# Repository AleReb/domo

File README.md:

# Domo — registrador ambiental para ESP32

Domo mide temperatura, humedad y presión, muestra lecturas en una pantalla OLED y guarda archivos CSV diarios en una tarjeta MicroSD. Este documento describe el comportamiento de [domo.ino](domo.ino).

## Componentes

| Componente | Función y configuración del firmware |
| --- | --- |
| SHT40 | Temperatura y humedad por I2C, dirección `0x44`. |
| HMP60 + ADS1115 | Temperatura en A0 y humedad en A1 del ADS1115 (`0x48`), con salidas analógicas de 0–1 V. Ganancia `GAIN_ONE` (rango ±4,096 V). |
| BME280 | Temperatura, humedad y presión por I2C, dirección `0x76`. |
| DHT22 | Temperatura y humedad por GPIO 19. |
| DS3231 | Fecha y hora para la pantalla y el registro. |
| OLED SH1106 de 128 × 64 | Dirección `0x3C`; controlador activo `U8G2_SH1106_128X64_NONAME_F_HW_I2C`. Hay una alternativa SSD1306 comentada en el código. |
| MicroSD | Almacenamiento por SPI, bus HSPI. |

Para el HMP60, el código convierte `temperatura (°C) = mV × 0,1 − 40` y `humedad (% HR) = mV × 0,1`, con humedad limitada a 0–100 %. Comprueba que estas fórmulas correspondan a la configuración de salida del sensor utilizado.

## Conexiones

`Wire.begin()` usa los pines I2C predeterminados de la placa seleccionada. Para el ESP32 Dev Module configurado en el repositorio:

| Interfaz | Señal | Pin ESP32 |
| --- | --- | --- |
| I2C compartido | SDA | GPIO 21 |
| I2C compartido | SCL | GPIO 22 |
| MicroSD / HSPI | MISO | GPIO 2 |
| MicroSD / HSPI | MOSI | GPIO 15 |
| MicroSD / HSPI | CLK | GPIO 14 |
| MicroSD / HSPI | CS | GPIO 13 |
| DHT22 | DATA | GPIO 19 |

Conecta la salida de temperatura del HMP60 a A0 del ADS1115 y la de humedad a A1, con tierra común. Comprueba alimentación, niveles eléctricos y conexiones antes de energizar el montaje. Esta tabla describe el firmware; revisa también el esquema electrónico.

## Compilación y puesta en marcha

1. Abre `domo.ino` desde una carpeta llamada `domo` en Arduino IDE.
2. Instala el paquete de placas **esp32 de Espressif Systems** y selecciona **ESP32 Dev Module** (`esp32:esp32:esp32`). Los artefactos incluidos hacen referencia al core **2.0.17**; las versiones de las bibliotecas no están fijadas en un manifiesto.
3. Instala las bibliotecas indicadas abajo y sus dependencias.
4. Selecciona el puerto de la placa, compila y carga el sketch. La configuración de VS Code está en [`.vscode/arduino.json`](.vscode/arduino.json); su puerto `COM1` debe ajustarse al equipo utilizado.
5. Abre el monitor serie a **115200 baudios** para revisar mensajes `[INIT]`, `[OK]`, `[ERR]`, `[ADS RAW]` y `[LOG]`. Envía `h` o `help` con un final de línea para ver instrucciones y el estado del equipo.
6. Espera el mensaje `[OK] RTC Found` y ajusta el DS3231 por serial como se indica abajo. El sketch no comprueba automáticamente `rtc.lostPower()`.
7. Inserta una MicroSD compatible con la biblioteca `SD` y verifica que aparezca `[LOG] Data written`.

| Biblioteca | Autor / proveedor | Cabeceras |
| --- | --- | --- |
| Adafruit ADS1X15 | Adafruit | `Adafruit_ADS1X15.h` |
| Adafruit BME280 Library | Adafruit | `Adafruit_BME280.h` |
| Adafruit Unified Sensor | Adafruit | `Adafruit_Sensor.h` |
| DHT sensor library | Adafruit | `DHT.h`, `DHT_U.h` |
| RTClib | Adafruit | `RTClib.h` |
| SHT4x | Rob Tillaart | `SHT4x.h` |
| U8g2 | olikraus / Oliver Kraus | `U8g2lib.h` |
| Adafruit BusIO | Adafruit | Dependencia de bibliotecas Adafruit |

`Arduino.h`, `Wire.h`, `SPI.h` y `SD.h` forman parte del core ESP32. El repositorio no incluye un archivo `platformio.ini`.

## Comandos por serial

Abre el monitor serie a **115200 baudios** y selecciona un final de línea **Nueva línea (LF)**, **Retorno de carro (CR)** o **Ambos (CRLF)**. Los comandos se ejecutan al recibir el final de línea.

| Comando | Función |
| --- | --- |
| `h` | Muestra la ayuda y el estado de inicialización de los componentes. |
| `help` | Equivalente a `h`. |
| `DD/MM/AAAA HH:MM:SS` | Ajusta la fecha y hora del RTC DS3231. |

### Ayuda y componentes del dispositivo

Escribe `h` o `help` en minúsculas y pulsa **Enviar**. La respuesta explica el ajuste de fecha y hora, muestra un ejemplo y enumera los componentes configurados: OLED SH1106, SHT40, ADS1115/HMP60, BME280, DS3231, DHT22 y MicroSD, con sus direcciones I2C o conexiones. También muestra la fecha y hora actual del RTC si está inicializado.

Los estados corresponden a las banderas de inicialización del firmware; no constituyen una comprobación continua de conexión física. La inicialización del ADS1115 no confirma la conexión del HMP60, y la del DHT22 no garantiza una lectura válida. Un componente pendiente puede estar ausente, haber fallado o estar esperando el próximo intento de inicialización.

### Ajuste de fecha y hora

Una vez que aparezca `[OK] RTC Found`, envía una línea con el formato exacto `DD/MM/AAAA HH:MM:SS`, usando hora de **24 horas**. Por ejemplo:

```text
29/10/2026 14:35:00
```

El firmware valida los días de cada mes, los años bisiestos y los rangos de hora (00–23), minutos y segundos (00–59). Se admiten años de **2000 a 2099**. Una línea inválida o demasiado larga, o un RTC sin inicializar, produce un mensaje `[ERR]` y no modifica la hora.

Al aceptar el comando, llama a `rtc.adjust()` y muestra `[OK] Fecha/hora enviada al RTC: 29/10/2026 14:35:00`. El próximo registro utiliza la fecha ajustada para seleccionar el archivo diario. No se convierte la zona horaria: introduce la hora que quieras mantener en el RTC. El formato del CSV permanece igual.

## Operación y formato CSV

Las tareas se programan con `millis()` y estos intervalos:

| Constante | Valor | Función |
| --- | --- | --- |
| `READ_INTERVAL_MS` | 2000 ms | Lectura de sensores. |
| `LOG_INTERVAL_MS` | 1000 ms | Escritura si SD y RTC están inicializados. |
| `DISPLAY_INTERVAL_MS` | 500 ms | Actualización de la OLED y salida de estado por serie cuando la OLED está inicializada. |
| `OLED_ROTATION_MS` | 20000 ms | Alternancia de pantallas: SHT40/DHT22 y HMP60/BME280. |
| `INIT_RETRY_MS` | 3000 ms | Intervalo mínimo entre intentos de inicialización. |

La escritura es más frecuente que la lectura: filas consecutivas pueden repetir una medición. El acceso a periféricos y los `delay()` pueden añadir demoras; los intervalos no garantizan tiempo real.

El archivo diario se crea en la raíz de la tarjeta como `YYYYMMDD.csv`, según la fecha del RTC. Se escribe una cabecera al crear un archivo nuevo y las filas se anexan. La cabecera actual es:

```csv
Timestamp,Timeon,SHT_Temp,SHT_Hum,HMP_Temp,HMP_Hum,RefBME_Temp,RefBME_RefHum,BME_Press,DHT_Temp,DHT_Hum
```

| Campo | Contenido |
| --- | --- |
| `Timestamp` | Fecha y hora del RTC: `YYYY-MM-DD HH:MM:SS`, sin zona horaria. |
| `Timeon` | Tiempo encendido: `on: HH:MM:SS`, calculado al actualizar la OLED. |
| `SHT_Temp`, `HMP_Temp`, `RefBME_Temp`, `DHT_Temp` | Temperatura en °C, con un decimal. |
| `SHT_Hum`, `HMP_Hum`, `RefBME_RefHum`, `DHT_Hum` | Humedad relativa en %, con un decimal. |
| `BME_Press` | Presión en hPa, con un decimal. |

`RefBME_RefHum` es el nombre generado actualmente por el código. Los datos no disponibles se representan como `nan`; una lectura fallida del SHT40 puede conservar el último valor válido.

## Limitaciones actuales

- La adquisición y la visualización pueden continuar con componentes ausentes, pero **sin RTC o sin SD no se guardan filas CSV**.
- El primer intento de inicialización está sujeto al intervalo de 3 segundos. La condición de reintento del bucle incluye OLED, SHT40, ADS1115, RTC y SD; no incluye BME280 ni DHT22. Estos últimos solo vuelven a intentarse mientras alguno de los componentes contemplados siga pendiente.
- La detección del DHT22 usa metadatos de la biblioteca y no confirma que el sensor esté conectado o responda.
- `Timeon` puede quedar vacío sin OLED: `upStr` se calcula en `updateOLED()`. El estado `SD LOG: OK` refleja la inicialización de la tarjeta, no confirma cada escritura ni la disponibilidad del RTC.
- No se implementan sincronización de hora por red ni recuperación de una SD desconectada después de inicializarse.

## Estructura

- [`domo.ino`](domo.ino): fuente del firmware.
- [`dataloggerDomo/`](dataloggerDomo/): esquema `domoLogger.sch`, placa `domoLogger.brd`, archivos de proyecto y respaldos EAGLE. Los archivos principales declaran EAGLE 9.6.2. Revisa su correspondencia con el firmware actual antes de fabricar.
- [`.vscode/`](.vscode/): configuración local de Arduino y del editor.
- [`build/`](build/): artefactos de una compilación anterior, con rutas locales y componentes de terceros. Compila desde `domo.ino` para obtener firmware actualizado.
- [`LICENSE`](LICENSE) y [`LICENSES/`](LICENSES/): alcance de las licencias y textos completos.

## Licencias

| Componente | Licencia | Alcance |
| --- | --- | --- |
| Hardware | **CERN-OHL-S-2.0** | Diseños propios y documentación de hardware en `dataloggerDomo/`. |
| Software | **GPL-3.0-only** | Software propio y documentación general del proyecto. |
| Firmware | **GPL-3.0-only** | `domo.ino` y código de firmware propio derivado. |

Consulta [LICENSE](LICENSE) para el alcance por componente y los textos completos de [CERN-OHL-S-2.0](LICENSES/CERN-OHL-S-2.0.txt) y [GPL-3.0-only](LICENSES/GPL-3.0-only.txt). GPL se aplica **solo en su versión 3**, sin la opción «o cualquier versión posterior».

Los componentes de terceros conservan sus licencias originales. La biblioteca EAGLE `diy-modules`, incorporada en los diseños, incluye un aviso **CC BY 4.0** de Miroslaw Brudnowski que se conserva. Las bibliotecas, el core ESP32 y sus artefactos compilados conservan sus respectivos términos.

Fuentes de los textos: [Open Hardware Repository / CERN](https://ohwr.org/licences/) y [GNU / Free Software Foundation](https://www.gnu.org/licenses/gpl-3.0.html).

El hardware, el software y el firmware se proporcionan sin garantías, conforme a las licencias respectivas.

## Autor

**Alejandro Rebolledo** — arebolledo@udd.cl

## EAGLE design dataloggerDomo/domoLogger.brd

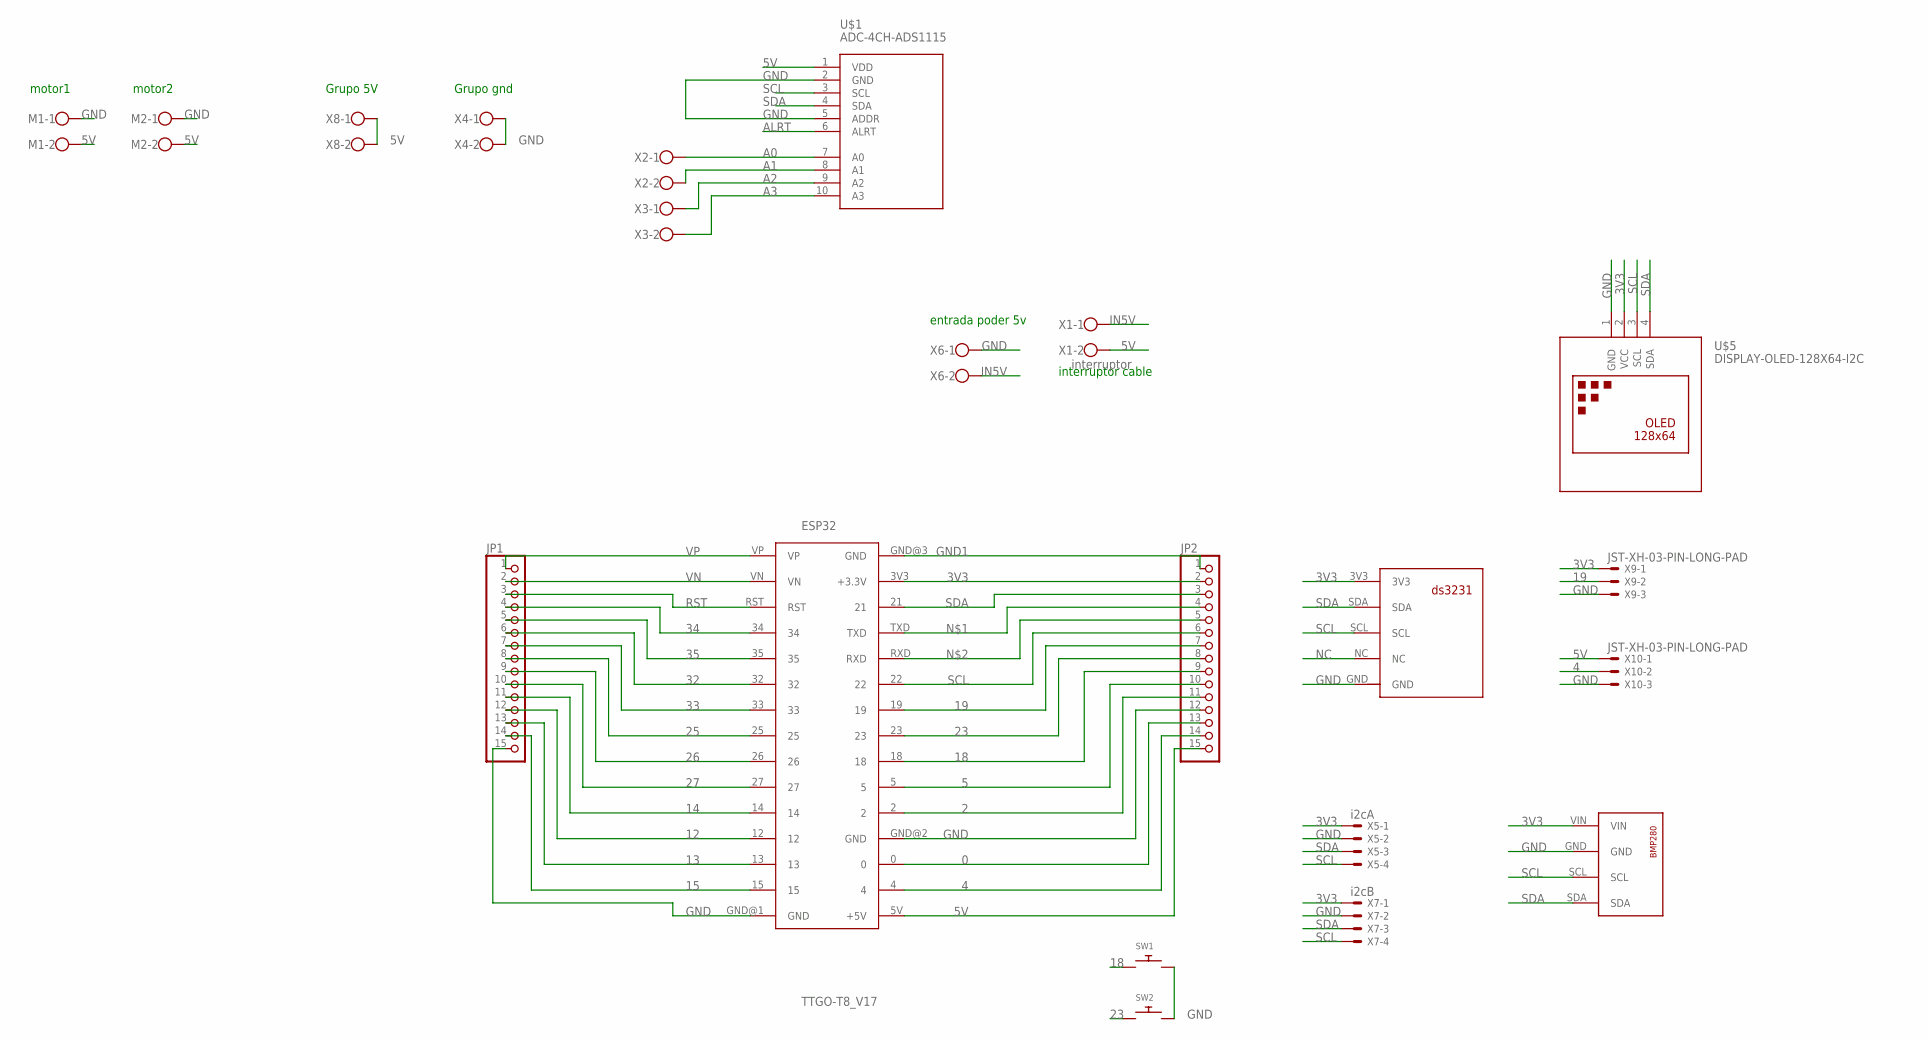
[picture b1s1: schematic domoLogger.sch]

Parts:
ESP32: TTGO-T8_V17
JP1, JP2: PINHD-1X15; 1X15
M1, M2: W237-102
SW1, SW2: SWITCH_PUSHBUTTONEVQ-PE; TACT_PANA-EVQ
U$1: ADC-4CH-ADS1115
U$3: GYBMEP_BMP280THROUGH_THE_HOLE; GYBMEP_BMP280
U$4: RTC; RTCDS3231FP
U$5: DISPLAY-OLED-128X64-I2C
X1: interruptor; W237-102
X2, X3, X4, X6, X8: W237-102
X5: i2cA; JST-XH-04-PACKAGE-LONG-PAD
X7: i2cB; JST-XH-04-PACKAGE-LONG-PAD
X9, X10: JST-XH-03-PIN-LONG-PAD; JST-XH-03-PACKAGE-LONG-PAD

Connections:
0: ESP32.0, JP2.13
2: ESP32.2, JP2.11
3V3: ESP32.3V3 (+3.3V), JP2.2, U$3.VIN, U$4.3V3, U$5.2 (VCC), X5.1, X7.1, X9.1
4: ESP32.4, JP2.14, X10.2
5: ESP32.5, JP2.10
5V: ESP32.5V (+5V), JP2.15, M1.2, M2.2, U$1.1 (VDD), X1.2, X8.1, X8.2, X10.1
12: ESP32.12, JP1.12
13: ESP32.13, JP1.13
14: ESP32.14, JP1.11
15: ESP32.15, JP1.14
18: ESP32.18, JP2.9, SW1.P$1
19: ESP32.19, JP2.7, X9.2
23: ESP32.23, JP2.8, SW2.P$1
25: ESP32.25, JP1.8
26: ESP32.26, JP1.9
27: ESP32.27, JP1.10
32: ESP32.32, JP1.6
33: ESP32.33, JP1.7
34: ESP32.34, JP1.4
35: ESP32.35, JP1.5
A0: U$1.7 (A0), X2.1
A1: U$1.8 (A1), X2.2
A2: U$1.9 (A2), X3.1
A3: U$1.10 (A3), X3.2
ALRT: U$1.6 (ALRT)
GND: ESP32.GND@1 (GND), ESP32.GND@2 (GND), JP1.15, JP2.12, M1.1, M2.1, SW1.P$2, SW2.P$2, U$1.2 (GND), U$1.5 (ADDR), U$3.GND, U$4.GND, U$5.1 (GND), X4.1, X4.2, X5.2, X6.1, X7.2, X9.3, X10.3
GND1: ESP32.GND@3 (GND), JP2.1
IN5V: X1.1, X6.2
unnamed: ESP32.TXD, JP2.4
unnamed: ESP32.RXD, JP2.5
NC: U$4.NC
RST: ESP32.RST, JP1.3
SCL: ESP32.22, JP2.6, U$1.3 (SCL), U$3.SCL, U$4.SCL, U$5.3 (SCL), X5.4, X7.4
SDA: ESP32.21, JP2.3, U$1.4 (SDA), U$3.SDA, U$4.SDA, U$5.4 (SDA), X5.3, X7.3
VN: ESP32.VN, JP1.2
VP: ESP32.VP, JP1.1

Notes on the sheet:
entrada poder 5v
interruptor cable
Grupo gnd
Grupo 5V
motor1
motor2

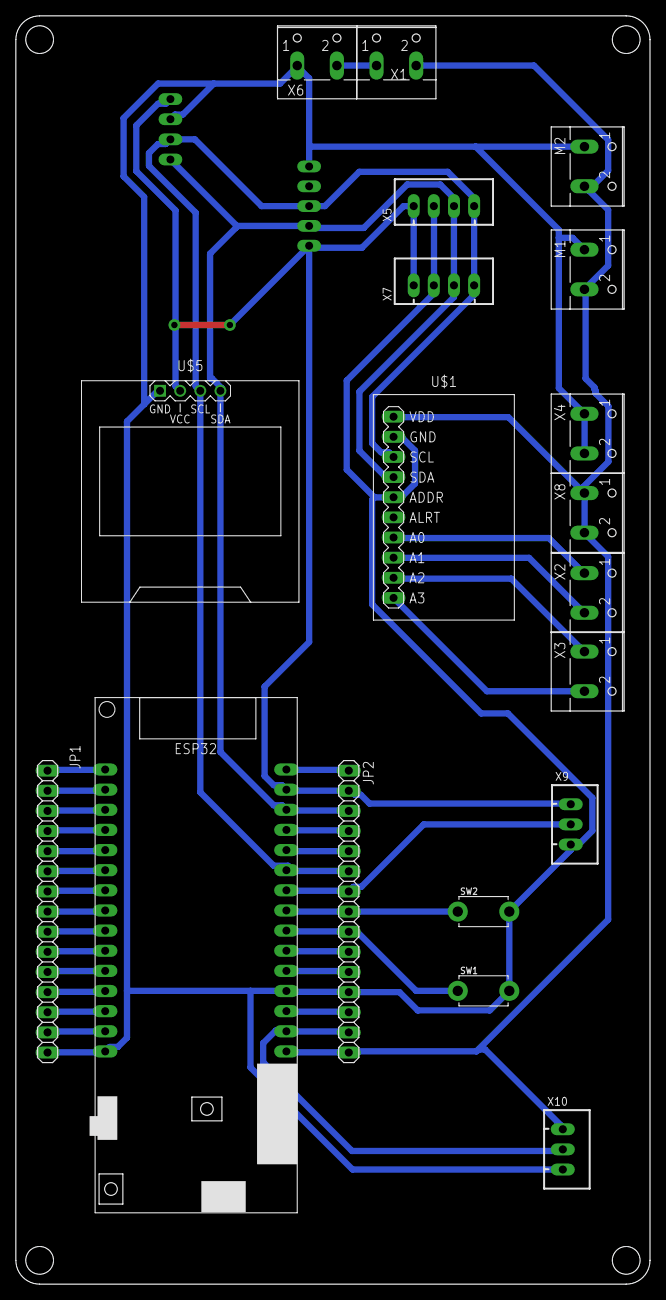
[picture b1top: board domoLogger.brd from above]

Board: 2 copper layers, 80.0 x 160.0 mm, 21 parts (1 on the bottom side), 34 nets.

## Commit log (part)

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2026-01-19 feat: Add VS Code Arduino configuration and implement uptime display on OLED with adjusted sensor layout.
2026-01-26 feat: Add VS Code configuration files and update the main Arduino sketch. add shematic and board pcb

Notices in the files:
parts and their libraries:
diy-modules: Released under the Creative Commons Attribution 4.0 International License: http://creativecommons.org/licenses/by/4.0
